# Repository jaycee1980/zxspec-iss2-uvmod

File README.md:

# ZX Spectrum Issue Two UV Mod

This is a a small modification board to add the autobias circuit for the U and V video signals, present in Issue 3 and later Spectrums, to an Issue 2 Spectrum.

It eliminates the annoying VR1 and VR2 trimmer potentiometers, and thus the need to "tune" the signal for a correct colour picture. This helps enormously as these settings often drift with temperature, and can drift with aging of the ULA. Some ULA's become impossible to "tune" as they age.

Additional thanks to Jim Smith of [Happy Little Diodes](https://www.youtube.com/c/HappyLittleDiodes) as he helped me develop this board. The original inspiration came from [one of his videos](https://www.youtube.com/watch?v=m4PCPcdD4Uw) and after watching it I wondered how do-able it was to adapt an Issue 2 board to use the autobias circuit from the Issue 3 and later, and whether it would help with the "untunaeable" ULA he had in the video.

I proposed prototyping a modification using a circuit on Veroboard, and he tested this out [here](https://www.youtube.com/watch?v=yTBOfa4Heks), including an early revision of the modification board. We revised it a bit so it was neater and easier to fit, and this is the result :)

In [this](https://www.youtube.com/watch?v=-wrouM9OnbY) video Jim shows the final version of the mod board fitted, including the ordering process with [PCBWay](https://www.pcbway.com)

# How to install it

* Solder some wires to the GND, 5V and Y terminals of the mod board PCB
* Remove R38, R39, R40, R41, R56, R63, C52, C53, VR1, VR2 from the Spectrum PCB
* Fit a 470 Ohm 1/4 watt resistor between the right hand terminal of R41, and a +5V supply. Refer to the picture below to see the recommended fitting.

* Fit some 2.54mm pitch header pins to the PCB, in the right hand holes where C52, R56, C53 and R63 were fitted (see picture)

* Fit the mod board so the header pins go through the appropriate holes on the mod board, and solder in place.
* Solder the wires to the Spectrum PCB to make the appropriate connections. GND can be found on the R63's left hand pad. 5V can be found on the bottom leg of the large 15 ohm resistor next to the ULA, and Y can be found on the Y link underneath the LM1889. Alternatively see the picture above for holes which carry the appropriate signals. You will need to remove some soldermask on the underside of the board if you use those.

The final result should look much like this:

# What's included here

Here you will find the EAGLE project files, a schematic, Gerber files, and BOM+CPL files for use with [JLCPCB](https://jlcpcb.com)'s self assembly service.

# Getting PCBs
Jim has a [PCBWay Shared Project](https://www.pcbway.com/project/shareproject/ZX_Spectrum_Issue_Two_UV_Mod_ba1552a4.html)

You can also have them made by [JLCPCB](https://jlcpcb.com) using the BOM, CPL and Gerber files provided

# License

This project is licensed under the [Creative Commons Attribution-NonCommercial-ShareAlike (CC BY-NC-SA)](https://creativecommons.org/licenses/by-nc-sa/4.0/) license.

I am not responsible for any Spectrums damaged due to fitting this mod!

If you want to sell prebuilt PCB's on your retro store, please contact me at github@dark-matter.me.uk. I will normally grant this provided they are sold for reasonable cost.

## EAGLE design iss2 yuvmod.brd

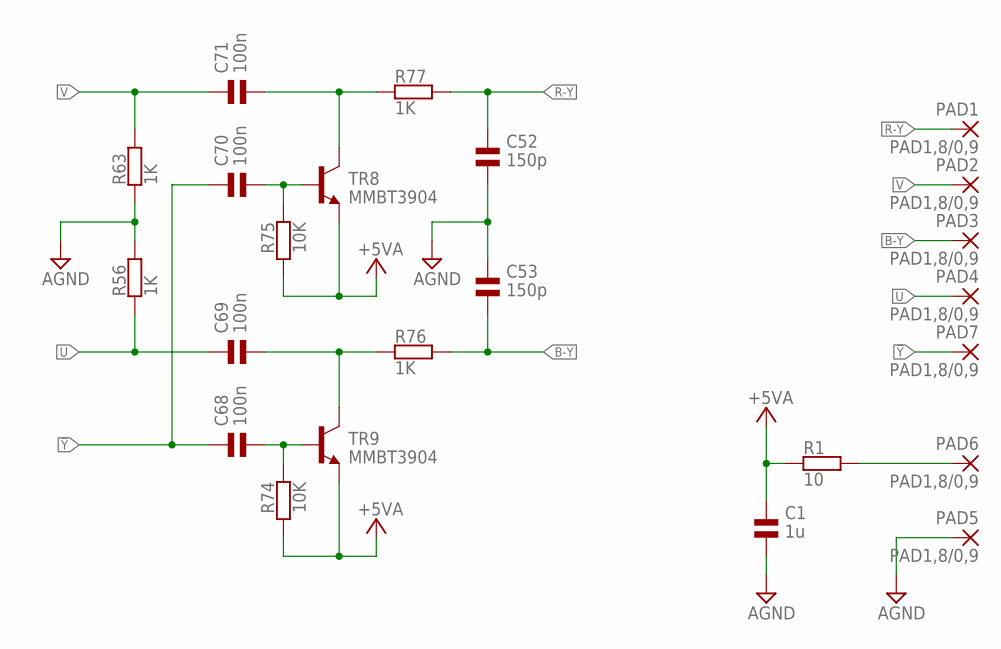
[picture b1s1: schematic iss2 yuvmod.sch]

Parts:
C1: 1u; 0603; LCSC_PART C15849
C52, C53: 150p; 0603; LCSC_PART C1594
C68, C69, C70, C71: 100n; 0603; LCSC_PART C14663
PAD1, PAD2, PAD3, PAD4, PAD5, PAD6, PAD7: PAD1,8/0,9; 1,8/0,9
R1: 10; 0603; LCSC_PART C22859
R56, R63, R76, R77: 1K; 0603; LCSC_PART C21190
R74, R75: 10K; 0603; LCSC_PART C25804
TR8, TR9: MMBT3904; SOT23; LCSC_PART C20526

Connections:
!Y: C68.1, C70.1, PAD7.1
+5VA: C1.1, R1.1, R74.2, R75.2, TR8.2 (E), TR9.2 (E)
AGND: C1.2, C52.2, C53.1, PAD5.1, R56.2, R63.1
B-Y: C53.2, PAD3.1, R76.2
unnamed: PAD6.1, R1.2
unnamed: C68.2, R74.1, TR9.1 (B)
unnamed: C70.2, R75.1, TR8.1 (B)
unnamed: C71.2, R77.1, TR8.3 (C)
unnamed: C69.2, R76.1, TR9.3 (C)
R-Y: C52.1, PAD1.1, R77.2
U: C69.1, PAD4.1, R56.1
V: C71.1, PAD2.1, R63.2

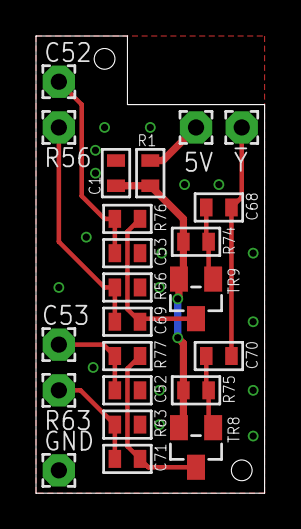
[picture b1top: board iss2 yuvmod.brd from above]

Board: 2 copper layers, 12.7 x 25.4 mm, 23 parts (0 on the bottom side), 12 nets.

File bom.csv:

Comment,Designator,Footprint,LCSC Part #
1K,R56 R63 R76 R77,0603,C21190
1u,C1,0603,C15849
10,R1,0603,C22859
10K,R74 R75,0603,C25804
100n,C68 C69 C70 C71,0603,C14663
150p,C52 C53,0603,C1594
MMBT3904,TR8 TR9,SOT23,C20526

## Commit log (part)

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2026-02-02 Add content
2026-02-02 Picture of replacement for R40
2026-02-02 Added annotation of where to find the 5V and Y signal holes in the PCB
2026-02-02 Cropped picture of built pcb's
2026-02-02 Cropped the image of the R40 replacement
2026-02-02 Create LICENSE
    Licensed under CC BY-NC-SA 4.0
2026-06-17 Correct picture showing where 5V and Y are - they were reversed!!!
